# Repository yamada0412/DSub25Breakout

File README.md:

# DSub25Breakout
DSub25Breakout

Ref:https://yamakashi.tech/?p=56

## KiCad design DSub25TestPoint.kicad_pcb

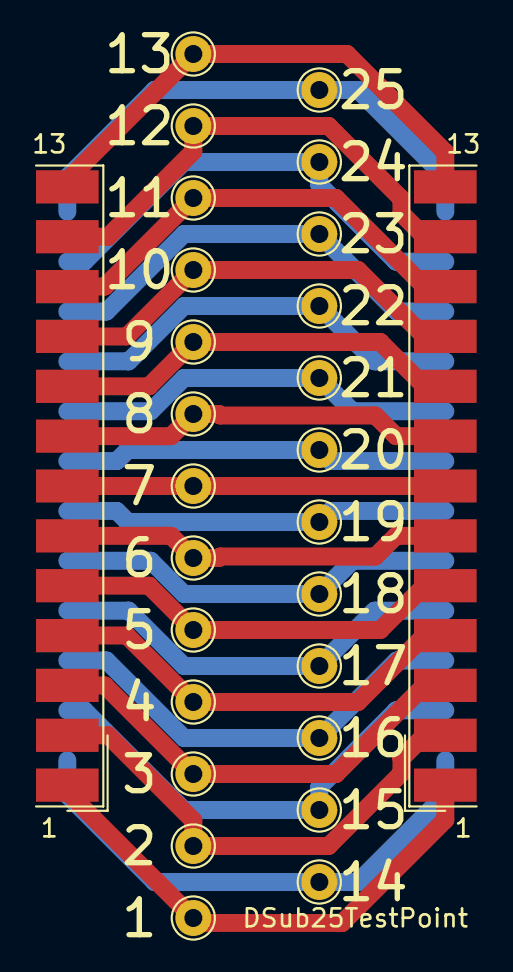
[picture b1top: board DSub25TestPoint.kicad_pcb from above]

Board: 2 copper layers, 27 parts (0 on the bottom side), 25 nets.

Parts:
1, 2, 3, 4, 5, 6, 7, 8, 9, 10, 11, 12, 13, 14, 15, 16, 17, 18, 19, 20, 21, 22, 23, 24, 25: TestPoint; TestPoint_THTPad_D2.0mm_Drill1.0mm
J1: DB25_Female; DSUB-25_Female_EdgeMount_P2.77mm
J2: DB25_Male; DSUB-25_Male_EdgeMount_P2.77mm

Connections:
P1: 1.1, J1.1, J2.1
P2: 2.1, J1.2, J2.2
P3: 3.1, J1.3, J2.3
P4: 4.1, J1.4, J2.4
P5: 5.1, J1.5, J2.5
P6: 6.1, J1.6, J2.6
P7: 7.1, J1.7, J2.7
P8: 8.1, J1.8, J2.8
P9: 9.1, J1.9, J2.9
P10: 10.1, J1.10, J2.10
P11: 11.1, J1.11, J2.11
P12: 12.1, J1.12, J2.12
P13: 13.1, J1.13, J2.13
P14: 14.1, J1.14, J2.14
P15: 15.1, J1.15, J2.15
P16: 16.1, J1.16, J2.16
P17: 17.1, J1.17, J2.17
P18: 18.1, J1.18, J2.18
P19: 19.1, J1.19, J2.19
P20: 20.1, J1.20, J2.20
P21: 21.1, J1.21, J2.21
P22: 22.1, J1.22, J2.22
P23: 23.1, J1.23, J2.23
P24: 24.1, J1.24, J2.24
P25: 25.1, J1.25, J2.25

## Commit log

2021-06-13 initial
    initial
